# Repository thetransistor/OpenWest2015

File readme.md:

# OpenWest 2015 Electronic Badge
[OpenWest](https://www.openwest.org/) and [theTransistor](http://thetransistor.com/) bring you another fun conference badge.

##Badge Parts List
- 1x Badge PCB
- 1x [ATTiny85](http://www.atmel.com/devices/attiny85.aspx)
- 1x 3xAAA Battery Holder
- 1x Push Button
- 1x Power Switch
- 5x RGB LEDs (WS2812b)
- 6x 0.1uF Capacitors, Ceramic
  
##Badge Add-On Kit Parts List
- 2x Button Board PCBs
- 1x [Parallax Propeller mCU](https://www.parallax.com/product/p8x32a-d40)
- 1x 40 Pin Socket for mCU
- 1x 2.2inch SPI TFT Display
  - [ILI9341 Controller](http://www.adafruit.com/datasheets/ILI9341.pdf)
  - 320x240 Resolution
- 1x 5mhz Crystal Oscillator (mCU runs at 80mhz) 
- 1x 24LC256 EEPROM
- 1x FTD434P MOSFET
- 1x 3.3v LDO Voltage Regulator
- 1x Tilt Switch
- 6x Push Buttons
- 1x Power Switch
- 10x 10k Resistors (labeled 103)
- 2x 10 ohm Resistors (labeled 100)
- 2x 1uF Ceramic Capacitors (with clear backing)
- 2x 0.1uF Ceramic Capacitors (with white backing)
- 1x 40 Pin Header Strip
- 1x SD to microSD Card Adapter
- 1x 128MB microSD Card

##Credits:

**Electronics Work & Processing**
- Compukidmike
- Devino

**Original Design**
- D3c4f

**QA, Assembly, & Loading**
- Animcogn
- Anthony (Demos)
- Trilog
- Nemus
- Evan (Sausage Assassin)
- Damon (Remote) 
- Compukidmike
- Yukaia
- D3c4f
- ProgrammerQ
- aarobc (l3mur)
- Tyrel
- AJ Oneal
- Jay (GraySands)

**Special Thanks**
- MindJuJu
- OpenWest Core Team
- This wonderful community!

##Questions and Comments
Questions and comments can be directed twards the following forms of communication:
- \#dc801 on freenode
- d3c4f [at] thetransistor [dot] com

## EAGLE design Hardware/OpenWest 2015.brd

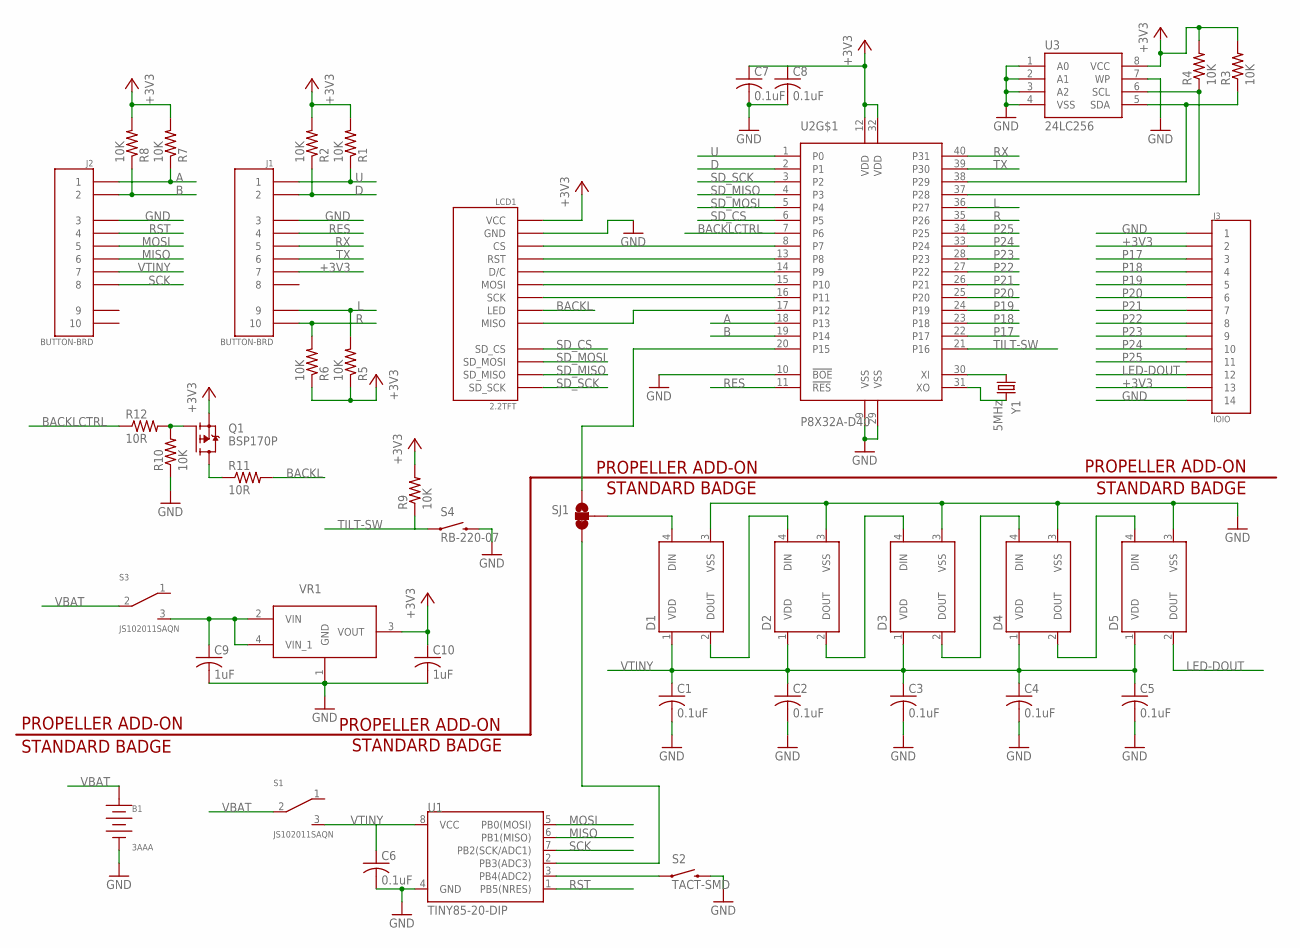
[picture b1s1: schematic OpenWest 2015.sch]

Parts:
B1: 3AAA; FLYING-LEADS
C1, C2, C3, C4, C5, C6, C7, C8: 0.1uF; C1206K
C9, C10: 1uF; C1206K
D1, D2, D3, D4, D5: WS2812B
J1, J2: BUTTON-BRD
J3: IOIO
LCD1: 2.2TFT
Q1: BSP170P; SOT223
R1, R2, R3, R4, R5, R6, R7, R8, R9, R10: 10K; R1206
R11, R12: 10R; R1206
S1, S3: JS102011SAQN; SAQN
S2: TACT-SMD
S4: RB-220-07; SPST
SJ1: JUMPER-PAD-3-2OF3_NC_BY_TRACE_LARGE; PAD-JUMPER-3-2OF3_NC_BY_TRACE_YES_SILK_LARGE
U1: TINY85-20-DIP; DIP08
U2: P8X32A-D40; DIP-40
U3: 24LC256; DIP08
VR1: MCP17-MCP1700T-3302E/MB; SOT150P400X160-4N
Y1: 5MHz; CRYSTAL-SMD

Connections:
+3V3: C7.1, C8.1, C10.1, J1.7, J3.P$2 (2), J3.P$13 (13), LCD1.VCC, Q1.3 (S), R1.2, R2.2, R3.2, R4.2, R5.1, R6.1, R7.2, R8.2, R9.2, U2.12 (VDD), U2.32 (VDD), U3.8 (VCC), VR1.3 (VOUT)
A: J2.1, R7.1, U2.18 (P13)
B: J2.2, R8.1, U2.19 (P14)
BACKL: LCD1.LED, R11.2
BACKLCTRL: R12.1, U2.7 (P6)
D: J1.2, R2.1, U2.2 (P1)
GND: B1.-, C1.2, C2.2, C3.2, C4.2, C5.2, C6.2, C7.2, C8.2, C9.2, C10.2, D1.3 (VSS), D2.3 (VSS), D3.3 (VSS), D4.3 (VSS), D5.3 (VSS), J1.3, J2.3, J3.P$1 (1), J3.P$14 (14), LCD1.GND, R10.1, S2.P$3 (2), S4.2, U1.4 (GND), U2.9 (VSS), U2.10 (!BOE), U2.29 (VSS), U3.1 (A0), U3.2 (A1), U3.3 (A2), U3.4 (VSS), U3.7 (WP), VR1.1 (GND)
L: J1.9, R5.2, U2.36 (P27)
LED-DOUT: D5.2 (DOUT), J3.P$12 (12)
MISO: J2.6, U1.6 (PB1(MISO))
MOSI: J2.5, U1.5 (PB0(MOSI))
unnamed: D1.4 (DIN), SJ1.2
unnamed: D1.2 (DOUT), D2.4 (DIN)
unnamed: D2.2 (DOUT), D3.4 (DIN)
unnamed: D3.2 (DOUT), D4.4 (DIN)
unnamed: D4.2 (DOUT), D5.4 (DIN)
unnamed: R4.1, U2.37 (P28), U3.6 (SCL)
unnamed: R3.1, U2.38 (P29), U3.5 (SDA)
unnamed: SJ1.3, U1.2 (PB3(ADC3))
unnamed: SJ1.1, U2.20 (P15)
unnamed: LCD1.CS, U2.8 (P7)
unnamed: LCD1.RST, U2.13 (P8)
unnamed: LCD1.D/C, U2.14 (P9)
unnamed: LCD1.MOSI, U2.15 (P10)
unnamed: LCD1.SCK, U2.16 (P11)
unnamed: LCD1.MISO, U2.17 (P12)
unnamed: U2.30 (XI), Y1.P$1 (1)
unnamed: U2.31 (XO), Y1.P$2 (2)
unnamed: C9.1, S3.3, VR1.2 (VIN), VR1.4 (VIN_1)
unnamed: S2.P$1 (1), U1.3 (PB4(ADC2))
unnamed: Q1.2 (D), Q1.4 (D), R11.1
unnamed: Q1.1 (G), R10.2, R12.2
P17: J3.P$3 (3), U2.22 (P17)
P18: J3.P$4 (4), U2.23 (P18)
P19: J3.P$5 (5), U2.24 (P19)
P20: J3.P$6 (6), U2.25 (P20)
P21: J3.P$7 (7), U2.26 (P21)
P22: J3.P$8 (8), U2.27 (P22)
P23: J3.P$9 (9), U2.28 (P23)
P24: J3.P$10 (10), U2.33 (P24)
P25: J3.P$11 (11), U2.34 (P25)
R: J1.10, R6.2, U2.35 (P26)
RES: J1.4, U2.11 (!RES)
RST: J2.4, U1.1 (PB5(NRES))
RX: J1.5, U2.40 (P31)
SCK: J2.8, U1.7 (PB2(SCK/ADC1))
SD_CS: LCD1.SD_CS, U2.6 (P5)
SD_MISO: LCD1.SD_MISO, U2.4 (P3)
SD_MOSI: LCD1.SD_MOSI, U2.5 (P4)
SD_SCK: LCD1.SD_SCK, U2.3 (P2)
TILT-SW: R9.1, S4.1, U2.21 (P16)
TX: J1.6, U2.39 (P30)
U: J1.1, R1.1, U2.1 (P0)
VBAT: B1.+, S1.2, S3.2
VTINY: C1.1, C2.1, C3.1, C4.1, C5.1, C6.1, D1.1 (VDD), D2.1 (VDD), D3.1 (VDD), D4.1 (VDD), D5.1 (VDD), J2.7, S1.3, U1.8 (VCC)

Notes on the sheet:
STANDARD BADGE
PROPELLER ADD-ON

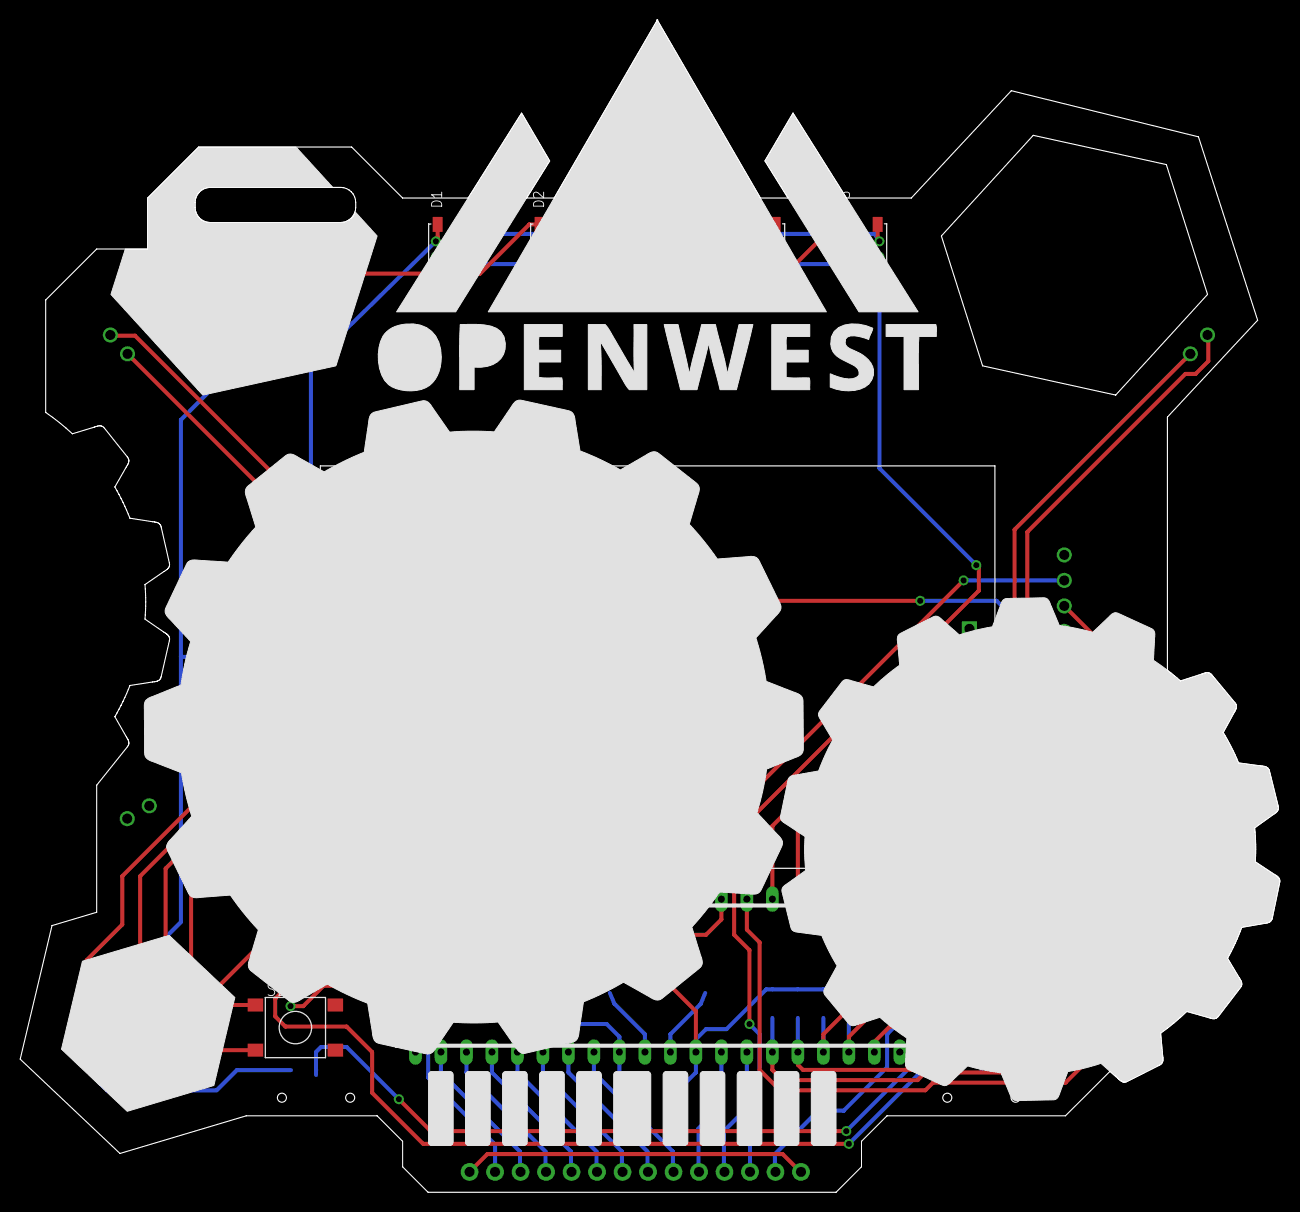
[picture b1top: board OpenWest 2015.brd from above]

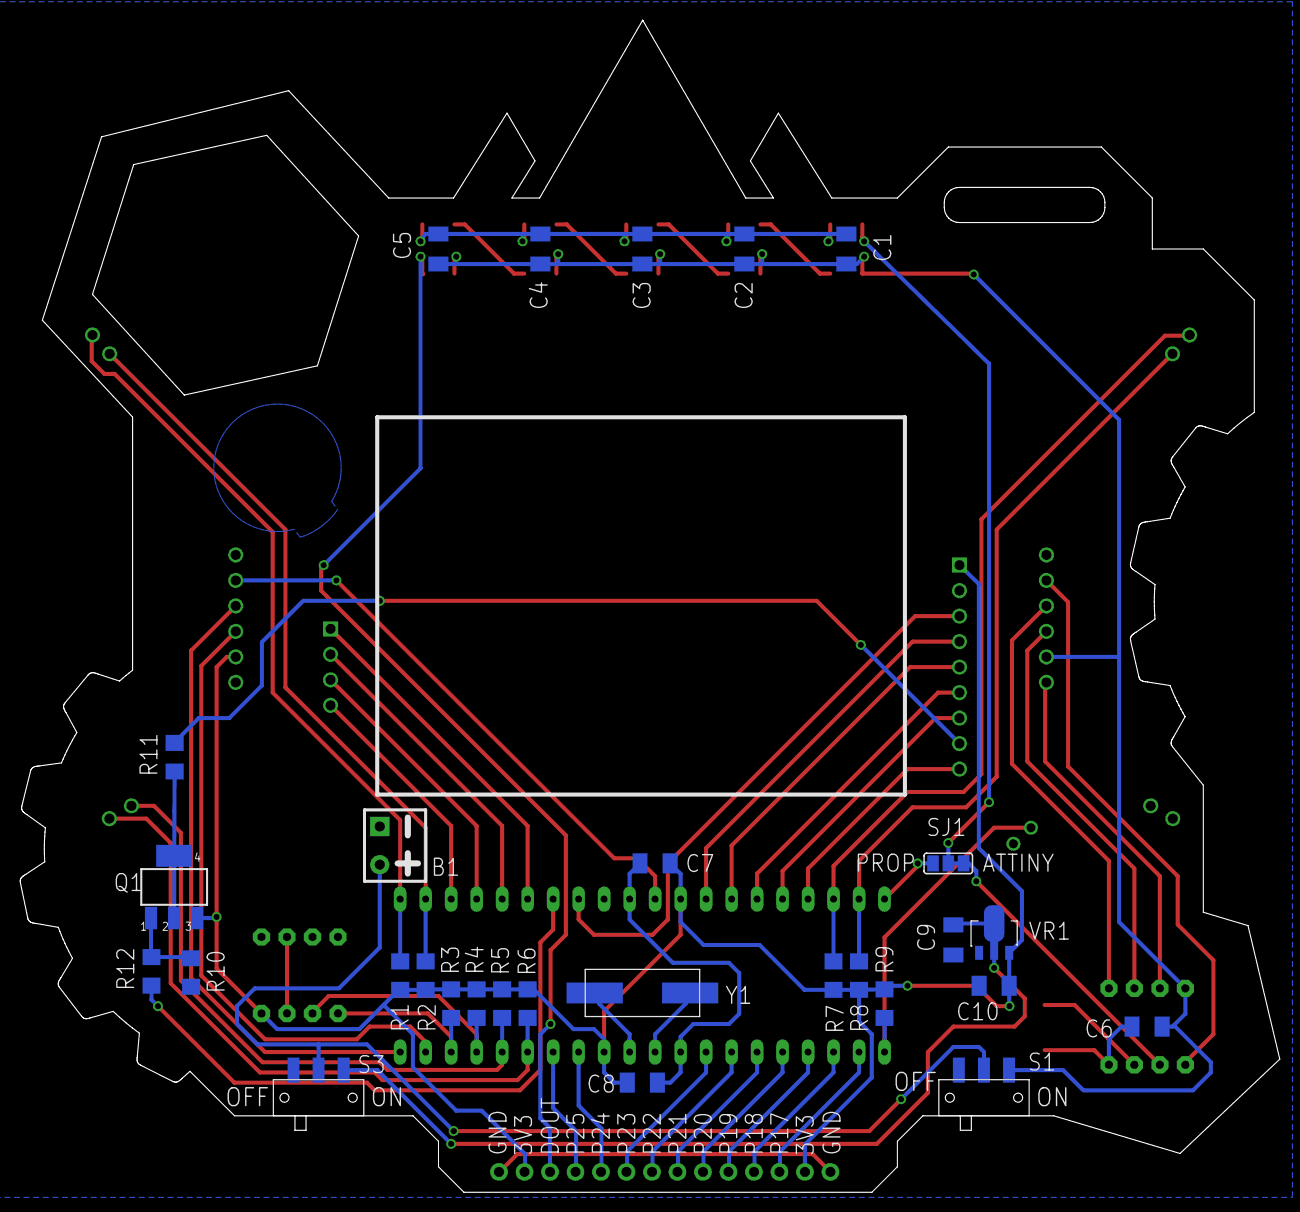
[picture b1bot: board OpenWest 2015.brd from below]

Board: 5 copper layers, 125.5 x 116.8 mm, 43 parts (30 on the bottom side), 55 nets.

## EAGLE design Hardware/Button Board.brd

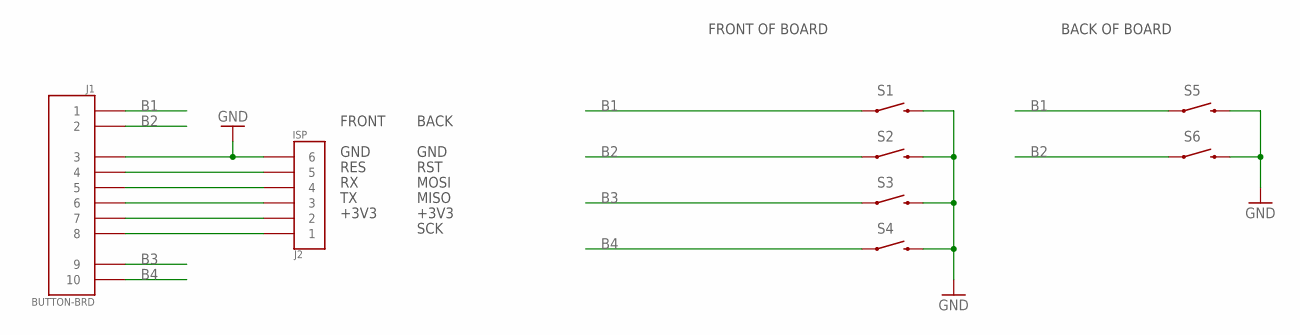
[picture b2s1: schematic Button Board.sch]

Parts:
J1: BUTTON-BRD
J2: ISP
S1, S2, S3, S4, S5, S6: TACT-SMD

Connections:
B1: J1.1, S1.P$1 (1), S5.P$1 (1)
B2: J1.2, S2.P$1 (1), S6.P$1 (1)
B3: J1.9, S3.P$1 (1)
B4: J1.10, S4.P$1 (1)
GND: J1.3, J2.P$6 (6), S1.P$3 (2), S2.P$3 (2), S3.P$3 (2), S4.P$3 (2), S5.P$3 (2), S6.P$3 (2)
unnamed: J1.4, J2.P$5 (5)
unnamed: J1.7, J2.P$2 (2)
unnamed: J1.5, J2.P$4 (4)
unnamed: J1.6, J2.P$3 (3)
unnamed: J1.8, J2.P$1 (1)

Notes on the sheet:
FRONT OF BOARD
BACK OF BOARD
FRONT
BACK
GND
+3V3
RES
MOSI
MISO
SCK
RST

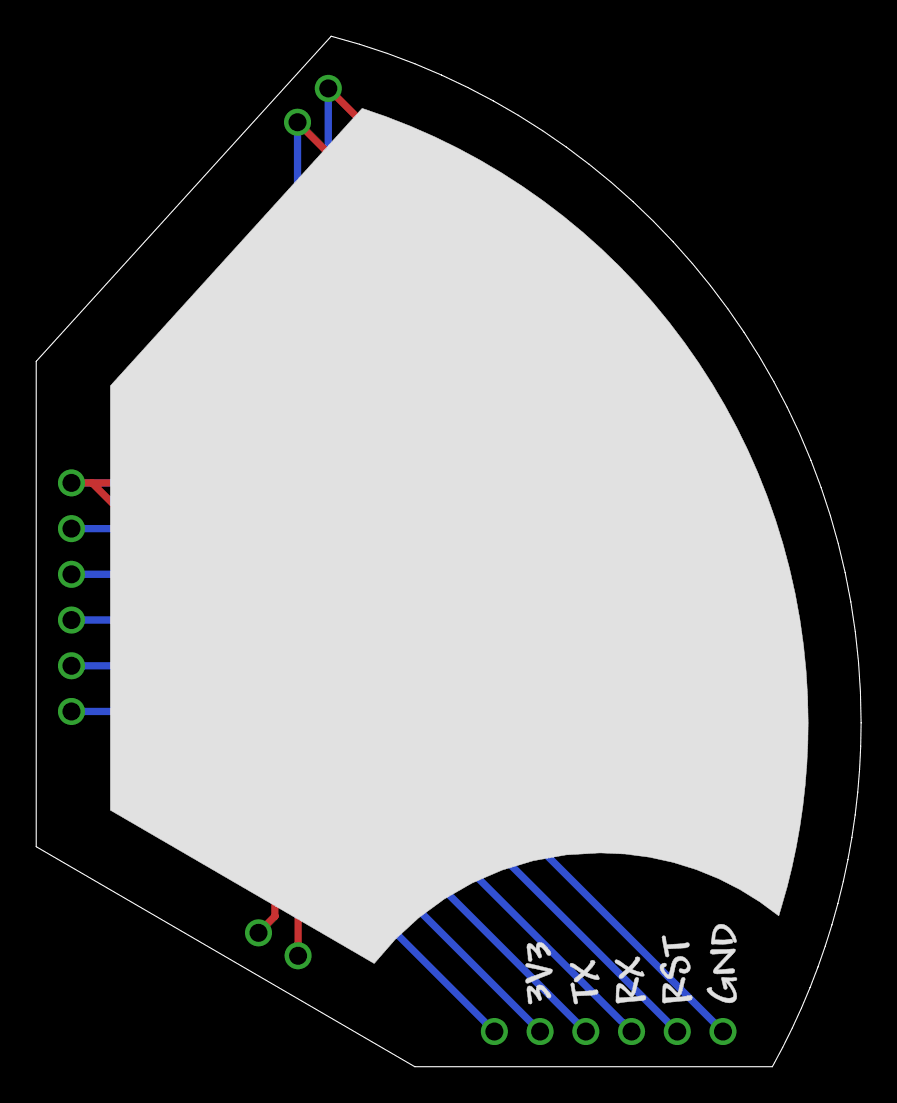
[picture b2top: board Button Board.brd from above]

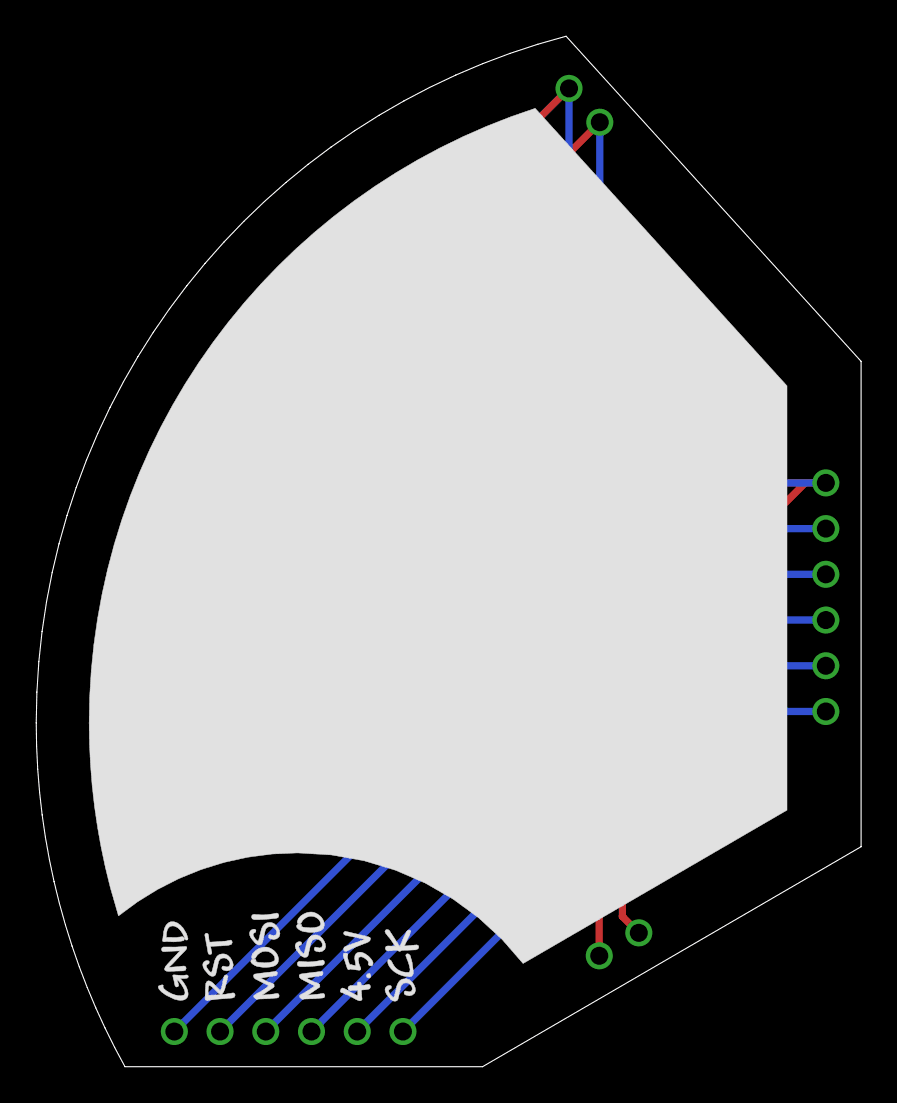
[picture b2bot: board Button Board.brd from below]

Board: 2 copper layers, 45.8 x 57.2 mm, 8 parts (2 on the bottom side), 10 nets.

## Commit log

2015-05-08 Initial Commit
    More to come, soon. :)
2015-05-08 Added default .gitignore
2015-05-08 Added readme
2015-05-08 Converted PDF to MD
    Converted PDF to MD to allow easier editing.
2015-05-08 Updated Images for Web
    Converted to PNG8
2015-05-08 Converted images for web
    Converted to save size / etc.
2015-05-08 Added addon kit instructions and BMP Loader Binary
2015-05-08 Updated BMP Loader, moved DemoCode.
2015-05-08 Added the IO Pinouts for the AddOn Kit
2015-05-08 fixed a typo
2015-05-09 image conversion script
2015-05-09 image conversion script for the lcd
2015-05-09 Create readme.md for add on
    Minimal - hopefully more to come.
2015-05-09 Fixed some assumptions
    After trying some previous assumptions appear not to be true.
2015-05-09 Button test project. Shows the state of buttons as you press them.
2015-05-09 Button test doc and info on writing your own code.
2015-05-09 added http to link to make it absolute
2015-05-09 Added an intro to Spin link to Writing Your Own Code
    I didn't see any resource introducing the Spin language, added a resource for that.
2015-05-09 Added an IO Test to test IO Pins and Buttons
2015-05-09 Added a link to SimpleIDE
2015-05-09 General cleanups and enhancements.
    I've removed bashisms and converted the script to a zsh script. I've
    added arguments so users can specify the input and output files. I
    added sanity checking around the input file.
2015-05-09 Updated deploy script to prompt for volume, and give user more feedback as to what is going on.
2015-05-09 Added prompt for disk name as well as volume, and show some help at the end to help people streamline the process in the future :)
2015-05-10 Added Add On Kit Images
2015-05-10 Converted the PDF to MD for easier editing and smaller file size.
2015-05-10 Fixed some formatting issues.
2015-05-10 Add updated spin files for the BMP Loader
2015-05-10 Move images into the img subdirectory
2015-05-10 Setup readme.md file with a basic description and instalation instructions
2015-05-10 Add notes and an example gif of exporting bmp images correctly.
2015-05-10 Clean up references to unneeded libraries, and unneeded code.
2015-05-13 Fix red background color issue on all pin states when pressing 'B' button.
2015-05-14 Adding Puzzle 15 to software
2015-05-14 Added run.bin file
    Compiled bluehawk's sweet sweet code.
2015-05-14 Added a readme to Puzzle 15 game.

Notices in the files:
parts and their libraries:
SparkFun-LED: Licensing: Creative Commons ShareAlike 4.0 International - https://creativecommons.org/licenses/by-sa/4.0
